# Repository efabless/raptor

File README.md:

#Overview

Raptor is a full SoC reference design for IoT applications based on the Arm Cortex M0 CPU core targeted on the X-FAB 
XH018 process (180nm).  Raptor provides means to interface with analog and digital sensors as well as external RF radio 
(WIFI, Cellular, Bluetooth, etc.,) modules needed for IoT applications.

The reference design is based on an SoC design template and can be modified, compiled and simulated through the SoC 
Editor tool with CloudV on the Efabless platform. The reference design comes with basic device drivers for all on-chip 
peripherals as well as set of applications to test and demonstrate Raptor capabilities.

Instances of the Raptor Design Template can be configured through the Design Request Form.   A configuration file is 
generated upon saving the form and can be used as a starting point for generating a reference design or to request a 
turn-key delivery of a custom SoC through design partners on the Efabless platform.

Below is the block diagram for a Demo Chip configuration taped-out for Raptor.  The design files for project include an 
instance of Raptor based on the configuration shown below.

##Project Contents
This project contains the design files for Raptor EVB, an evaluation board with a fully implemented SoC based on the 
Raptor template.  The pcba design files are based on Kicad.

The project also contains firmware example code using the Raptor EVB board.

#Hardware

#Firmware

The firmware examples can be built from their respective directories through the makefile.  The building the image files
requires install the gcc arm compiler.  Download install packages for the compiler can be found on the [Arm Developer 
Web Site](https://developer.arm.com/tools-and-software/open-source-software/developer-tools/gnu-toolchain/gnu-rm/downloads).

###To program the SPI flash chip:

  1. Install the pyftdi python library
  
    pip3 install pyftdi
  
  2. Configure the board for flash programming.

    Install jumpers on across pins 2 & 3 on the four 3-pin headers 
    next to the USB connector.
    
    Ensure the jumper for usb to Raptor uart are not installed 
    (two 2-pin headers next to USB)

  3. Change to the directory for the target firmware

    make clean hex flash

  4. Configure the board for processor operation

    Move jumpers on across pins 1 & 2 on the four 3-pin headers 
    next to the USB connector.

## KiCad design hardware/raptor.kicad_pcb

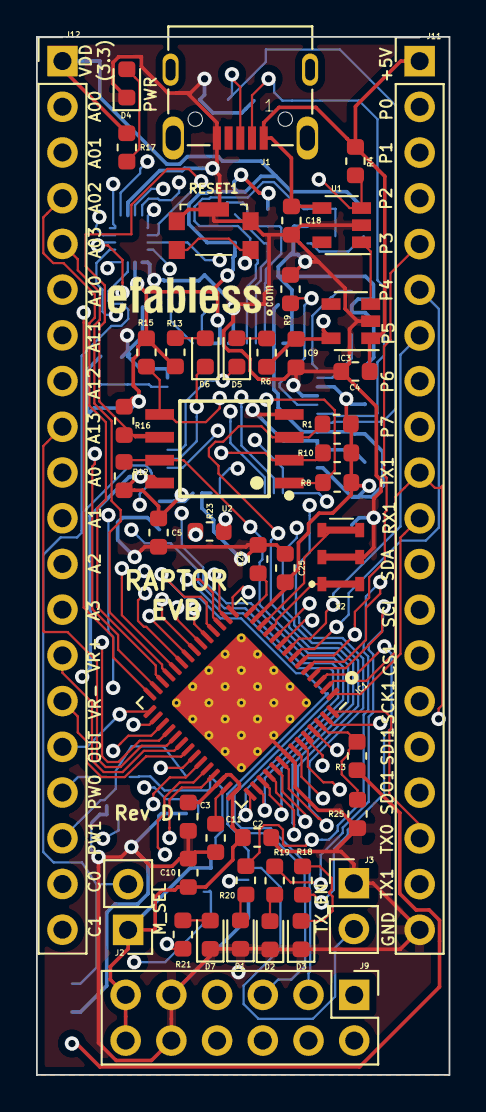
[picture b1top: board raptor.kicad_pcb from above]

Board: 4 copper layers, 22.9 x 57.7 mm, 72 parts (0 on the bottom side), 91 nets.

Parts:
C1: 10nf; C_0603_1608Metric
C2, C3, C5, C8, C10, C11, C15, C16, C17, C20, C21, C22, C25, C26: 0.1uf; C_0603_1608Metric
C4, C9, C18: 1uf; C_0603_1608Metric
D1, D2, D3, D4, D5, D6, D7: LED; LED_0603_1608Metric
FUSE1: PGB10100603; Fuse_0603_1608Metric
FUSE_0: PGB10100603; Fuse_0603_1608Metric
G1: LOGO; logo
IC1: RAPTORQFN56; QFN-56-1EP_8x8mm_P0.5mm_EP5.6x5.6mm_ThermalVias
IC2: FT232H; LQFP-48_7x7mm_P0.5mm
IC3: MCP1755; SOT-23-5
IC4: 93C56; SOT-23-6
IC5: TMUX1574RSVR; QFN40P180X260X55-16N
J1: USB; 629105150521
J2, J3: Conn_01x02_Male; PinHeader_1x02_P2.54mm_Vertical
J9: 2X6 FEMALE; PinHeader_2x06_P2.54mm_Vertical
J11, J12: CONN_20; PinHeader_1x20_P2.54mm_Vertical
R1, R3, R4, R5, R8, R10, R11, R12, R15, R16, R24: 10K; R_0603_1608Metric
R2, R14, R22: 10k; R_0603_1608Metric
R6, R13, R17, R18, R19, R20, R21: 150; R_0603_1608Metric
R7: 2K 1%; R_0603_1608Metric
R9: 12K 1%; R_0603_1608Metric
R23, R25: 0; R_0603_1608Metric
RESET1: SPST-SMD-4.6X2.8mm; TL6330AF200Q
U1: MCP1316M; SOT-23-5
U2: W25Q32FV; SOIC127P790X216-8N
U3: SN74LVC1G125DCKR; SOT65P210X110-5N
U4, U5: SN74LV1T34DCKR; SOT65P210X110-5N
X1: CSTNE12M0GH5L000R0
X2: CSTCR6M25G55B-R0; CSTCR6M25G55BR0

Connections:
+5V: C4.1, C18.1, IC3.1, J1.1, J11.1, R4.2, U1.4
/A00: IC1.28, J12.2
/A0: IC1.24, J12.10
/A01: IC1.27, J12.3
/A1: IC1.23, J12.11
/A02: IC1.26, J12.4
/A2: IC1.22, J12.12
/A03: IC1.25, J12.5
/A3: IC1.21, J12.13
/A10: IC1.30, J12.6
/A11: IC1.31, J12.7
/A12: IC1.32, J12.8
/A13: IC1.33, J12.9
/AOUT: IC1.29, J12.16
/C0: IC1.20, J12.19
/C1: IC1.19, J12.20
/CS0: IC1.16, J9.1
/MCS1: IC1.37, J11.14
/MEM_CS: IC5.2, R8.2, U2.1
/MEM_SCK: IC5.10, R16.2, U2.6
/MEM_SI: IC5.7, R15.2, U2.5
/MEM_SO: IC5.5, R10.2, U2.2
/MSCK1: IC1.36, J11.15
/MSI0: IC1.18, J9.5
/MSI1: IC1.39, J11.16
/MSO0: IC1.17, J9.3
/MSO1: IC1.38, J11.17
/P0: IC1.3, J9.2, J11.2, R18.2
/P1: IC1.4, J9.4, J11.3, R19.2
/P2: IC1.5, J11.4, R20.2
/P3: IC1.6, J11.5, R21.2
/P4: IC1.7, J11.6
/P5: IC1.8, J11.7
/P6: IC1.9, J11.8
/P7: IC1.10, J11.9
/PWM0: IC1.53, U4.2
/PWM0_LV: J12.17, U4.4
/PWM1: IC1.52, U5.2
/PWM1_LV: J12.18, U5.4
/RAPTOR_CS: IC1.43, IC5.16
/RAPTOR_D0: IC1.48, IC5.9
/RAPTOR_D1: IC1.47, IC5.3
/RAPTOR_D2: IC1.46, R1.2, U2.3
/RAPTOR_D3: IC1.45, R12.2, U2.7
/RAPTOR_SCK: IC1.44, IC5.12
/RX0: IC1.55, R23.2
/RX1: IC1.1, J11.11
/SCK0: IC1.15, J9.7
/SCL: IC1.50, J9.6, J11.13
/SDA: IC1.51, J9.8, J11.12
/TMUX_SEL: IC2.21, IC5.15, J2.2, R11.1
/TX0: IC1.56, J11.18, U3.2
/TX1: IC1.2, J11.10, J11.19
/TXD_EN: IC2.25, J3.2, R24.1, U3.1
/USB_CS: IC2.16, IC5.1
/USB_SCK_TXD: IC2.13, IC5.11, R23.1
/USB_SI: IC2.15, IC5.4
/USB_SO_RXD: IC2.14, IC5.8, U3.4
/VREF+: IC1.34, J12.14
/VREF-: IC1.35, J12.15
GND: C1.2, C2.2, C3.2, C4.2, C5.1, C8.1, C9.2, C10.2, C11.2, C15.1, C16.2, C17.2, C18.2, C20.2, C21.2, C22.1, C25.2, C26.2, D1.1, D2.1, D3.1, D4.1, D7.1, FUSE1.1, FUSE_0.1, IC1.49, IC1.57, IC2.4, IC2.9, IC2.10, IC2.11, IC2.22, IC2.23, IC2.35, IC2.36, IC2.41, IC2.42, IC2.47, IC2.48, IC3.2, IC4.2, IC5.6, IC5.13, J1.5, J3.1, J9.9, J9.10, J11.20, R9.1, R11.2, R25.1, RESET1.1, RESET1.2, RESET1.5, U1.2, U2.4, U3.3, U4.3, U5.3, X1.2, X2.2
unnamed: C1.1, IC2.34, R5.1
unnamed: C8.2, IC2.37
unnamed: C11.1, IC1.41
unnamed: C22.2, IC2.38
unnamed: C26.1, IC1.14
unnamed: D1.2, R20.1
unnamed: D2.2, R19.1
unnamed: D3.2, R18.1
unnamed: D4.2, R17.1
unnamed: D5.1, IC2.27
unnamed: D5.2, R6.2
unnamed: D6.1, IC2.26
unnamed: D6.2, R13.2
unnamed: D7.2, R21.1
unnamed: FUSE1.2, IC2.6, J1.2
unnamed: FUSE_0.2, IC2.7, J1.3
unnamed: IC1.11, X2.1
unnamed: IC1.12, X2.3
unnamed: IC1.54, R3.1, R25.2
unnamed: IC2.1, X1.1
unnamed: IC2.2, X1.3
unnamed: IC2.5, R9.2
unnamed: IC2.43, IC4.1, R7.1, R22.2
unnamed: IC2.44, IC4.4, R2.2
unnamed: IC2.45, IC4.5, R14.2
unnamed: IC3.3, U1.1
unnamed: IC4.3, R7.2
unnamed: J1.SHELL, J1.SHELL1, J1.SHELL2, J1.SHELL3
unnamed: R4.1, RESET1.3, RESET1.4, U1.3
VDD: C2.1, C3.1, C5.2, C9.1, C10.1, C15.2, C16.1, C17.1, C20.1, C21.1, C25.1, IC1.13, IC1.40, IC1.42, IC2.3, IC2.8, IC2.12, IC2.24, IC2.39, IC2.40, IC2.46, IC3.5, IC4.6, IC5.14, J2.1, J9.11, J9.12, J12.1, R1.1, R2.1, R3.2, R5.2, R6.1, R8.1, R10.1, R12.1, R13.1, R14.1, R15.1, R16.1, R17.2, R22.1, R24.2, U2.8, U3.5, U4.5, U5.5

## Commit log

2020-01-25 add spi_ftdi_flasher
2020-01-26 update PID for raptor FTDI
2020-01-27 flash startup edits
2020-01-27 raptor_flash.py added
2020-01-28 debug firmware; gpio
2020-01-30 add flash targt to make
2020-02-03 add hex file
2020-02-03 add test_30
2020-02-04 fixing raptor_flash.py
2020-02-05 support for cypress flash in raptor_flash.py
2020-02-05 add SRL
2020-02-05 blink = led test
2020-02-05 add test1
2020-02-05 fix test1
2020-02-05 fix make
2020-02-05 add support for microchip
2020-02-06 testing permanent SRL
2020-02-10 updatingg flash script for SST26
2020-02-11 added workaround for winbond flash
2020-02-11 fix blink.c
2020-03-10 add uart test
2020-03-17 added hardware and gitignore
2020-03-19 update schematic
2020-03-24 adjusted logo on silkscreen
2020-03-24 Revert "adjusted logo on silkscreen"
    This reverts commit 2ac67c38
2020-03-24 update logo and silkscreen (2)
2020-04-01 recommit previous version
2020-04-01 updated cut layer to include slots
2020-04-21 updated firmware build
2020-04-28 memory debug final commit and cleanup
2020-04-30 uart complete
2020-05-01 adc first pass working
2020-05-01 i2c + updated to flash
2020-05-06 completed dac and spi testing
2020-05-06 completed pwm testing
2020-05-15 adding check-bug script
2020-05-15 update check_bug in makefiles
2020-05-16 implement code workaround
2020-06-26 raptor hardware rev c
2020-06-26 update hardware libs
2020-07-01 updated blink and i2c with workaround fix
2020-08-08 updated raptor evb rev d
2020-08-08 update base address; clk_ctl to 50MHz w/ ext + PLL
2020-08-18 add directory for fpga
2020-09-05 updated files
2020-09-06 added second pass for code_workaround.py to catch push/pop w/ more than 6 args
2020-09-06 added message to check_bug.py for PASS vs FAIL
2020-09-06 implemented multi-pass logic for code_workaround.py
2020-09-07 fix for issue with multi-pass and code_workaround.py
2020-09-10 fix issue with tabs in code_workaround.py
2020-11-04 change to raptor.c; added functions to set clock using int and ext osc
